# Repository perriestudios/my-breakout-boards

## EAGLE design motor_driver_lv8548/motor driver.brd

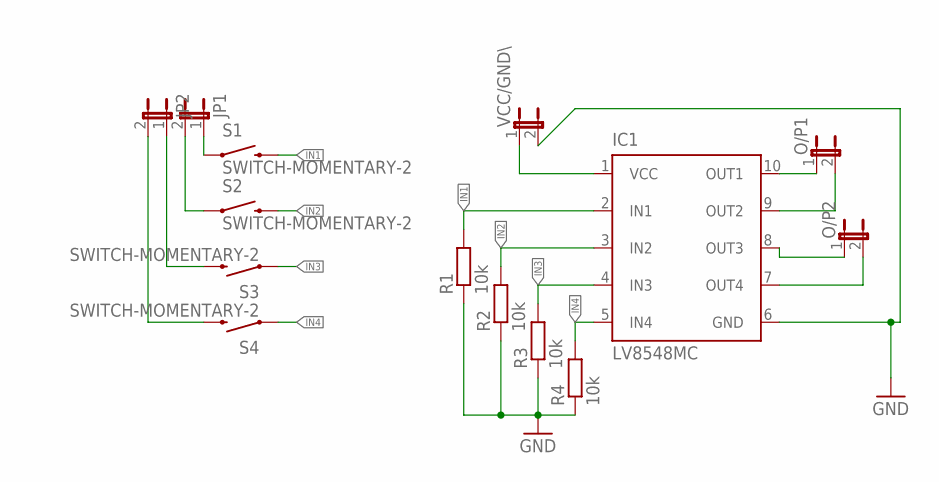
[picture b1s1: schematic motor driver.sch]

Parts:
IC1: LV8548MC; MFP10S
JP1, JP2: JP1E; JP1
O/P1, O/P2: JP1E; JP1
R1, R2, R3, R4: 10k; R0603
S1, S2, S3, S4: SWITCH-MOMENTARY-2; TACTILE_SWITCH_TALL
VCC/GND\: JP1E; JP1

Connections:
GND: IC1.6 (GND), R1.1, R2.1, R3.1, R4.1, VCC/GND\.2
IN1: IC1.2 (IN1), R1.2, S1.B2 (2)
IN2: IC1.3 (IN2), R2.2, S2.B2 (2)
IN3: IC1.4 (IN3), R3.2, S3.A2 (1)
IN4: IC1.5 (IN4), R4.2, S4.A2 (1)
unnamed: JP1.1, S1.A2 (1)
unnamed: JP1.2, S2.A2 (1)
unnamed: IC1.10 (OUT1), O/P1.1
unnamed: IC1.9 (OUT2), O/P1.2
unnamed: IC1.8 (OUT3), O/P2.1
unnamed: IC1.7 (OUT4), O/P2.2
unnamed: IC1.1 (VCC), VCC/GND\.1
unnamed: JP2.1, S3.B2 (2)
unnamed: JP2.2, S4.B2 (2)

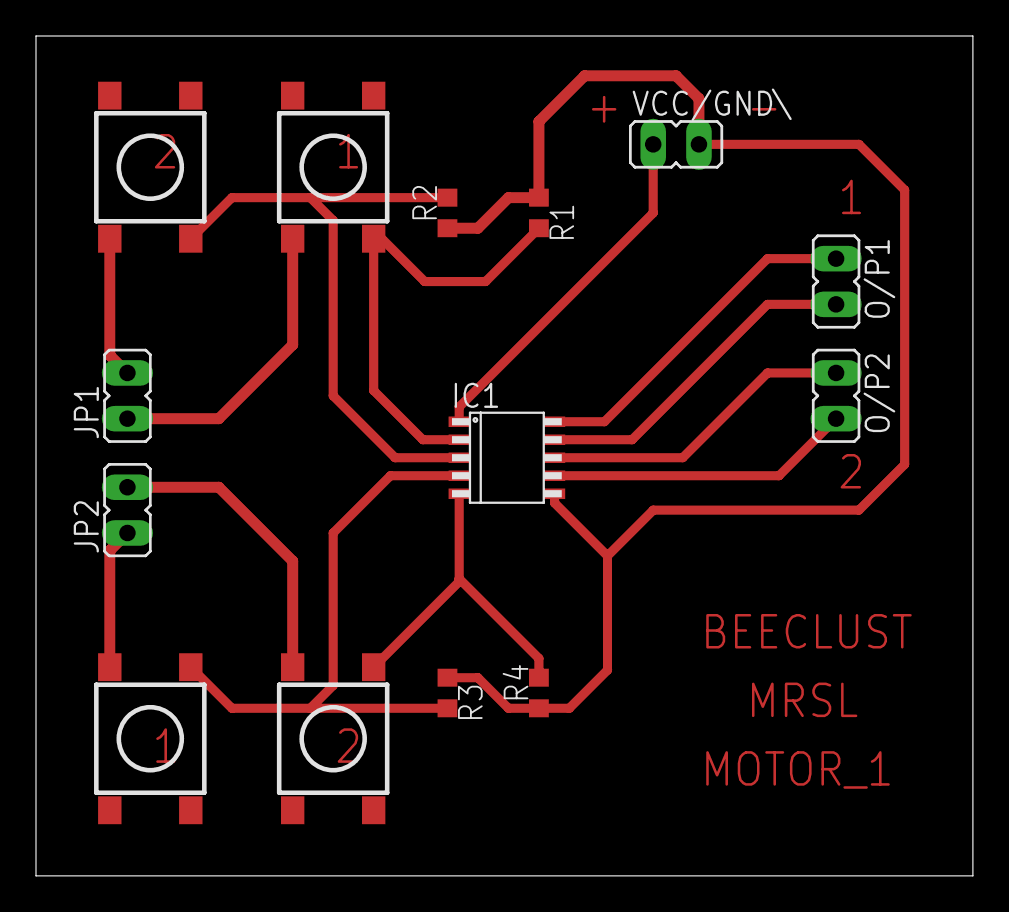
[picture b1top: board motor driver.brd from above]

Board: 2 copper layers, 52.0 x 46.7 mm, 14 parts (0 on the bottom side), 14 nets.

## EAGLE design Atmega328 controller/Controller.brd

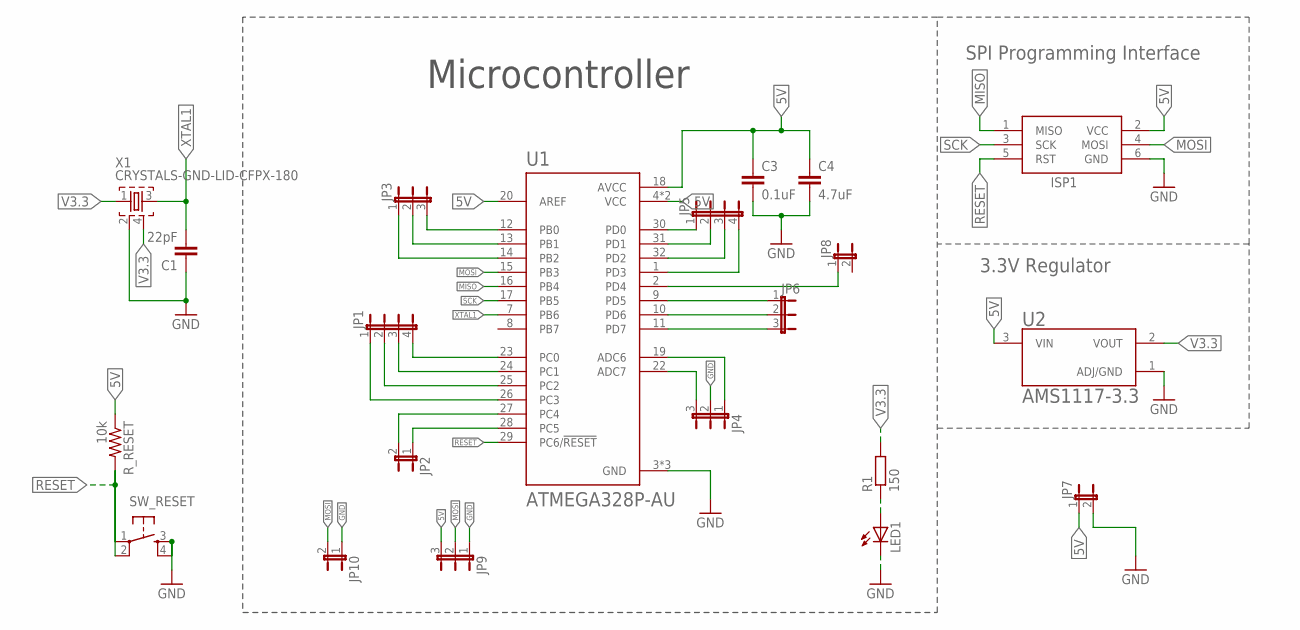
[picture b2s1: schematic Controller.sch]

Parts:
C1: 22pF; 0603-CAP
C3: 0.1uF; 0603-CAP
C4: 4.7uF; 0603-CAP
ISP1: AVRISP-6; AVRISP
JP1, JP5: JP4E; JP4
JP2, JP7, JP8, JP10: JP1E; JP1
JP3, JP4, JP6, JP9: JP2E; JP2
LED1: LEDSML0603; SML0603
R1: 150; R0603
R_RESET: 10k; 0603-RES
SW_RESET: TAC_SWITCHPTH; TACTILE-PTH
U1: ATMEGA328P-AU; QFP80P900X900X120-32N
U2: AMS1117-3.3; SOT229P700X180-4N
X1: CRYSTALS-GND-LID-CFPX-180; 3.4X2.7-4-PAD

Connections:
5V: C3.1, C4.1, ISP1.2 (VCC), JP7.1, JP9.3, R_RESET.1, U1.4 (VCC), U1.6 (VCC), U1.18 (AVCC), U1.20 (AREF), U2.3 (VIN)
GND: C1.1, C3.2, C4.2, ISP1.6 (GND), JP4.2, JP7.2, JP9.1, JP10.1, LED1.C, SW_RESET.3, SW_RESET.4, U1.3 (GND), U1.5 (GND), U1.21 (GND), U2.1 (ADJ/GND), X1.2
MISO: ISP1.1 (MISO), U1.16 (PB4)
MOSI: ISP1.4 (MOSI), JP9.2, JP10.2, U1.15 (PB3)
unnamed: LED1.A, R1.1
unnamed: JP1.4, U1.23 (PC0)
unnamed: JP1.3, U1.24 (PC1)
unnamed: JP1.2, U1.25 (PC2)
unnamed: JP1.1, U1.26 (PC3)
unnamed: JP2.2, U1.27 (PC4)
unnamed: JP2.1, U1.28 (PC5)
unnamed: JP3.3, U1.12 (PB0)
unnamed: JP3.2, U1.13 (PB1)
unnamed: JP3.1, U1.14 (PB2)
unnamed: JP4.3, U1.22 (ADC7)
unnamed: JP4.1, U1.19 (ADC6)
unnamed: JP5.1, U1.30 (PD0)
unnamed: JP5.2, U1.31 (PD1)
unnamed: JP5.3, U1.32 (PD2)
unnamed: JP5.4, U1.1 (PD3)
unnamed: JP8.1, U1.2 (PD4)
unnamed: JP6.1, U1.9 (PD5)
unnamed: JP6.2, U1.10 (PD6)
unnamed: JP6.3, U1.11 (PD7)
RESET: ISP1.5 (RST), R_RESET.2, SW_RESET.2, U1.29 (PC6/!RESET)
SCK: ISP1.3 (SCK), U1.17 (PB5)
V3.3: R1.2, U2.2 (VOUT), X1.1, X1.4
XTAL1: C1.2, U1.7 (PB6), X1.3

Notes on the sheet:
Microcontroller
SPI Programming Interface
3.3V Regulator

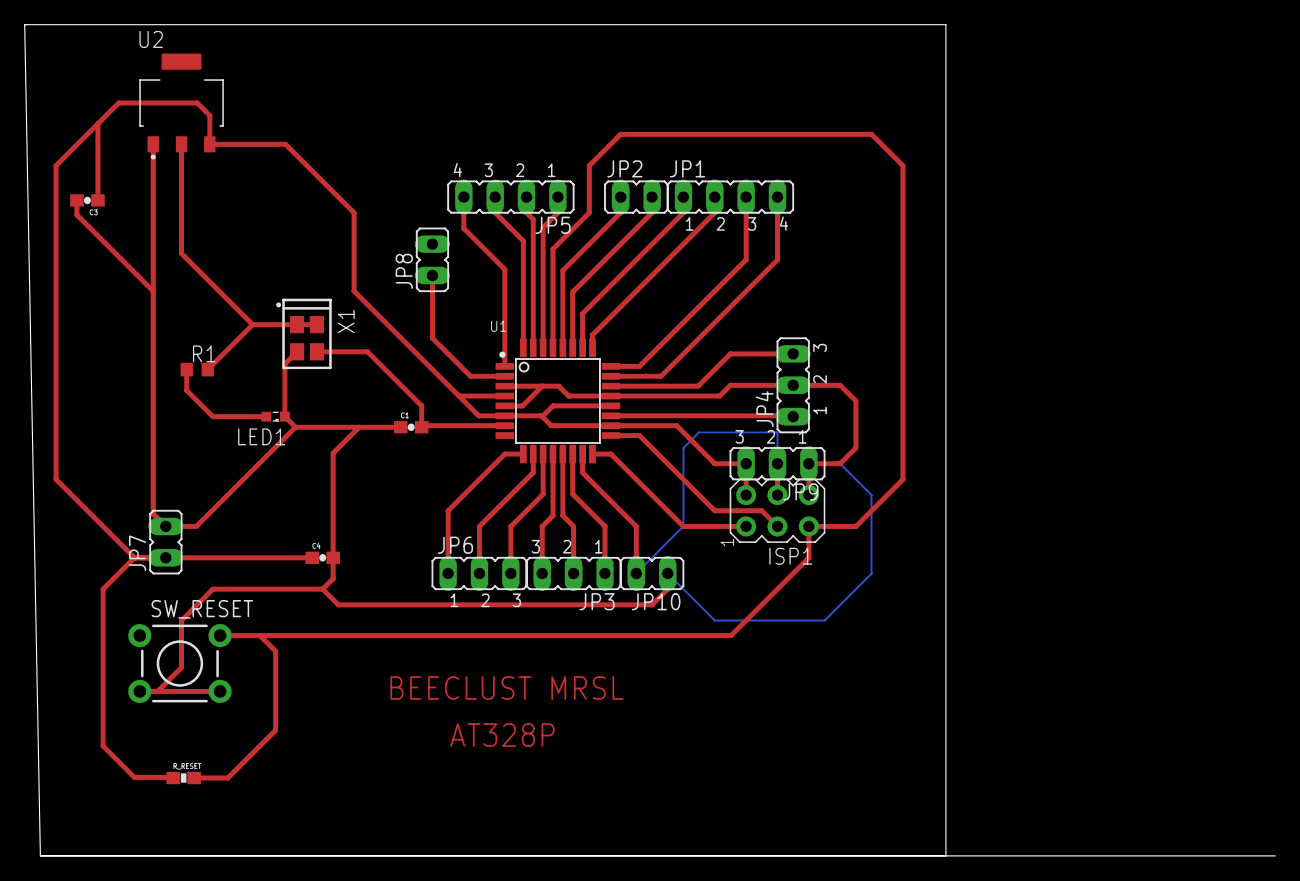
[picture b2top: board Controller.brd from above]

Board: 2 copper layers, 101.3 x 67.3 mm, 21 parts (0 on the bottom side), 28 nets.

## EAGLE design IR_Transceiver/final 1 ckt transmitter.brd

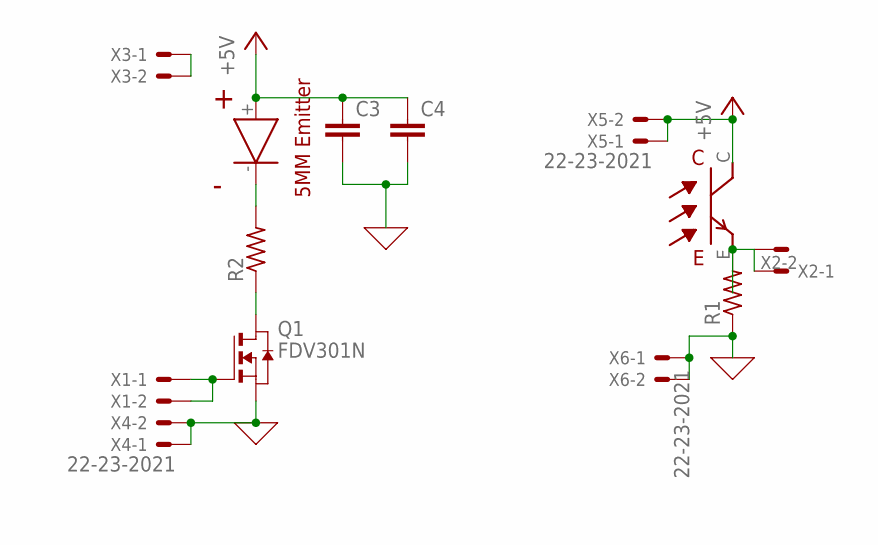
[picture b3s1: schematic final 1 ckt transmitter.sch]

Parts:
C3, C4: CAP0603-CAP; 0603-CAP
Q1: FDV301N; SOT-23
R1, R2: R-US_R0201; R0201
U$1: RECEIVER
U$3: EMITTER
X1, X2, X3, X4, X5, X6: 22-23-2021

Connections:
0: C3.2, C4.2, Q1.P$2 (S), R1.1, X4.1, X4.2, X6.1, X6.2
+5V: C3.1, C4.1, U$3.+
unnamed: Q1.P$3 (D), R2.1
unnamed: R1.2, U$1.E, X2.1, X2.2
unnamed: Q1.P$1 (G), X1.1, X1.2
unnamed: R2.2, U$3.-
unnamed: U$1.C, X5.1, X5.2
unnamed: X3.1, X3.2

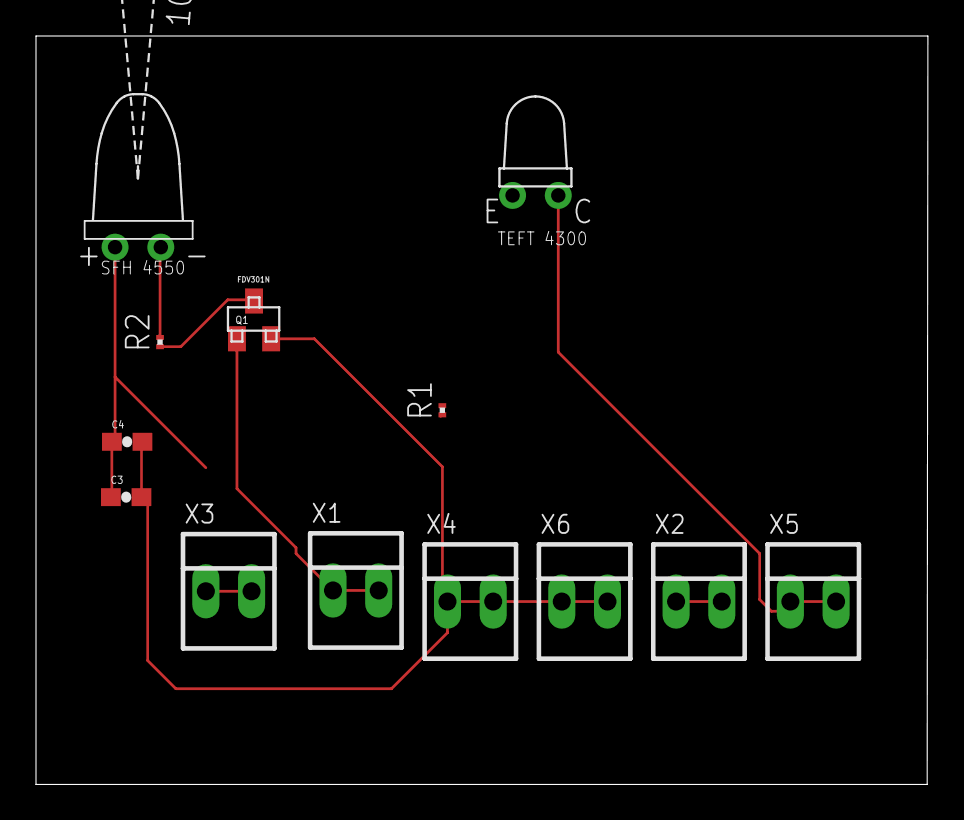
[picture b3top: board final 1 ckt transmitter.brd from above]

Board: 2 copper layers, 49.6 x 41.6 mm, 13 parts (0 on the bottom side), 8 nets.

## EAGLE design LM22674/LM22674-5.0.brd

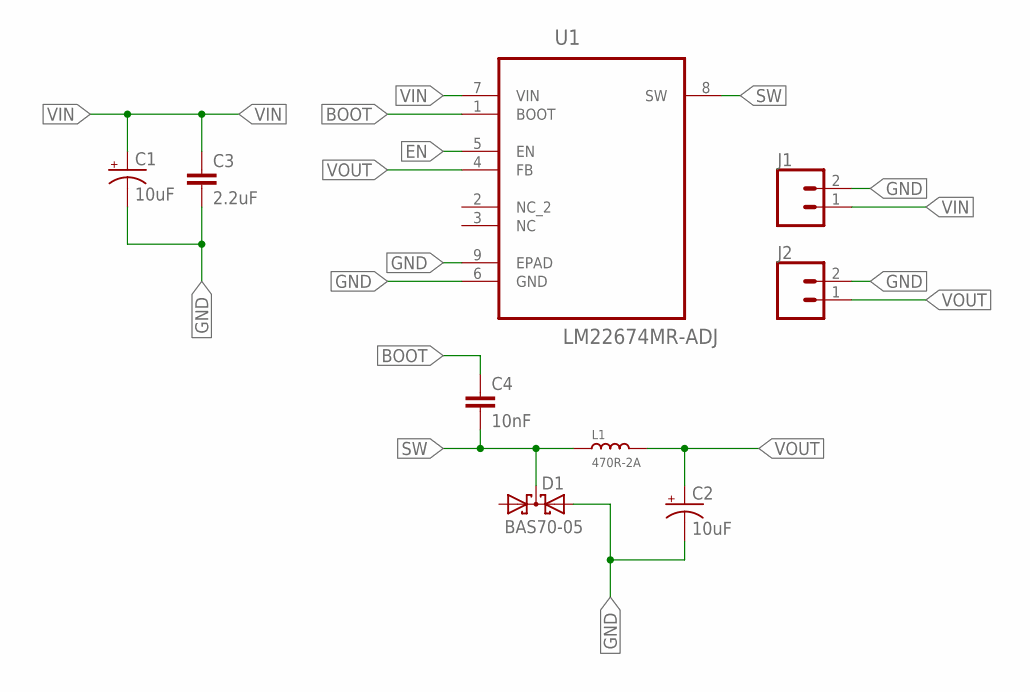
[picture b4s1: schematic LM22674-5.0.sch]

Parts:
C1, C2: 10uF; EIA3216
C3: 2.2uF; 0603
C4: 10nF; 0603
D1: BAS70-05; SOT23
J1, J2: CONN_02PTH4; 1X02_XTRA_BIG
L1: 470R-2A; L0805
U1: LM22674MR-ADJ; SOIC127P600X168-9N

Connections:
BOOT: C4.1, U1.1 (BOOT)
EN: U1.5 (EN)
GND: C1.-, C2.-, C3.2, D1.2 (A2), J1.2, J2.2, U1.6 (GND), U1.9 (EPAD)
SW: C4.2, D1.3 (C), L1.1, U1.8 (SW)
VIN: C1.+, C3.1, J1.1, U1.7 (VIN)
VOUT: C2.+, J2.1, L1.2, U1.4 (FB)

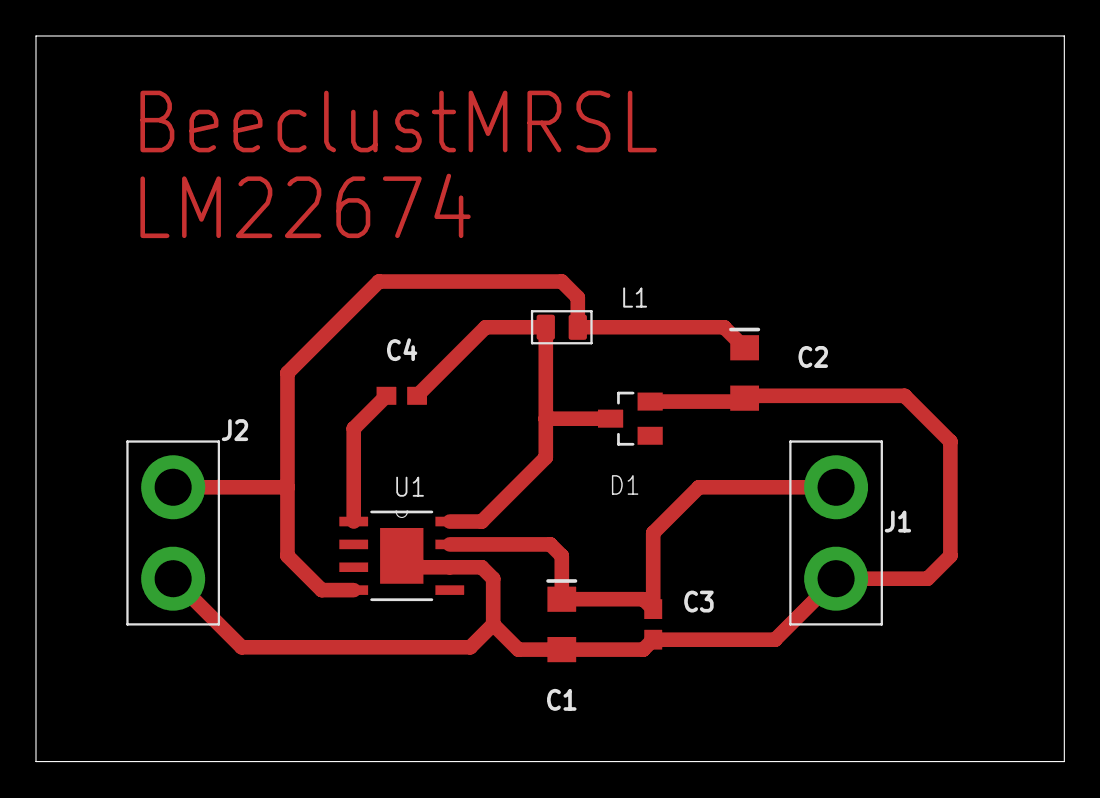
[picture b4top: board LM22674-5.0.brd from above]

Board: 2 copper layers, 57.1 x 40.3 mm, 9 parts (0 on the bottom side), 5 nets.

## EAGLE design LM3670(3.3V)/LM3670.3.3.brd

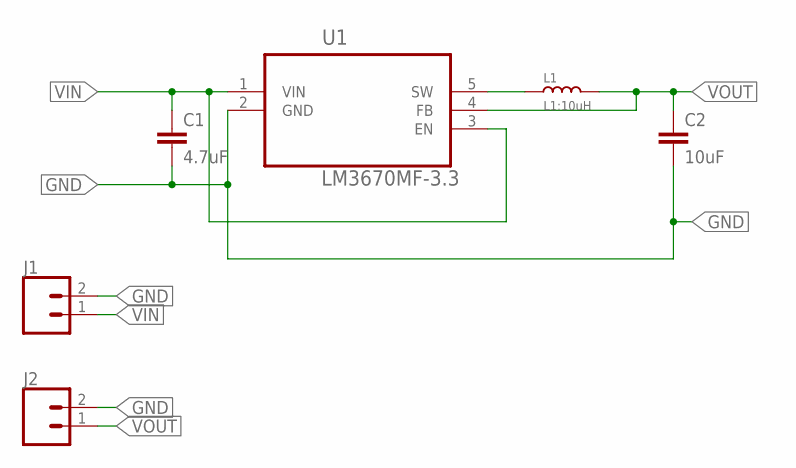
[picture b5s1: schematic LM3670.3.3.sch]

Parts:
C1: 4.7uF; 0603
C2: 10uF; 0805
J1, J2: CONN_02; 1X02
L1: L1:10uH; L0603
U1: LM3670MF-3.3; SOT95P284X122-5N

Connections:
GND: C1.2, C2.2, J1.2, J2.2, U1.2 (GND)
unnamed: L1.1, U1.5 (SW)
VIN: C1.1, J1.1, U1.1 (VIN), U1.3 (EN)
VOUT: C2.1, J2.1, L1.2, U1.4 (FB)

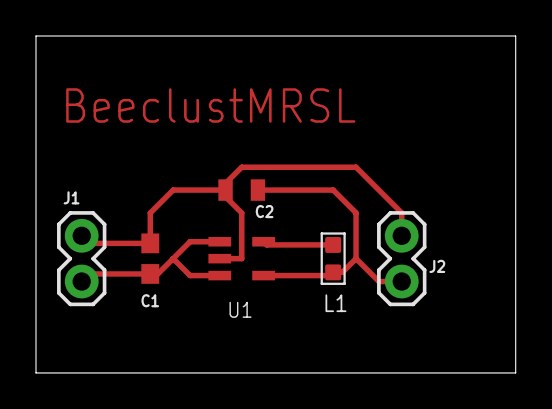
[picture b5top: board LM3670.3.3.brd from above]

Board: 2 copper layers, 26.6 x 18.7 mm, 6 parts (0 on the bottom side), 4 nets.

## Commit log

2020-11-17 Added the files

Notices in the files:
parts and their libraries:
SparkFun: Licensing: CC v3.0 Share-Alike You are welcome to use this library for commercial purposes.
SparkFun-Capacitors: Licensing: Creative Commons ShareAlike 4.0 International - https://creativecommons.org/licenses/by-sa/4.0
